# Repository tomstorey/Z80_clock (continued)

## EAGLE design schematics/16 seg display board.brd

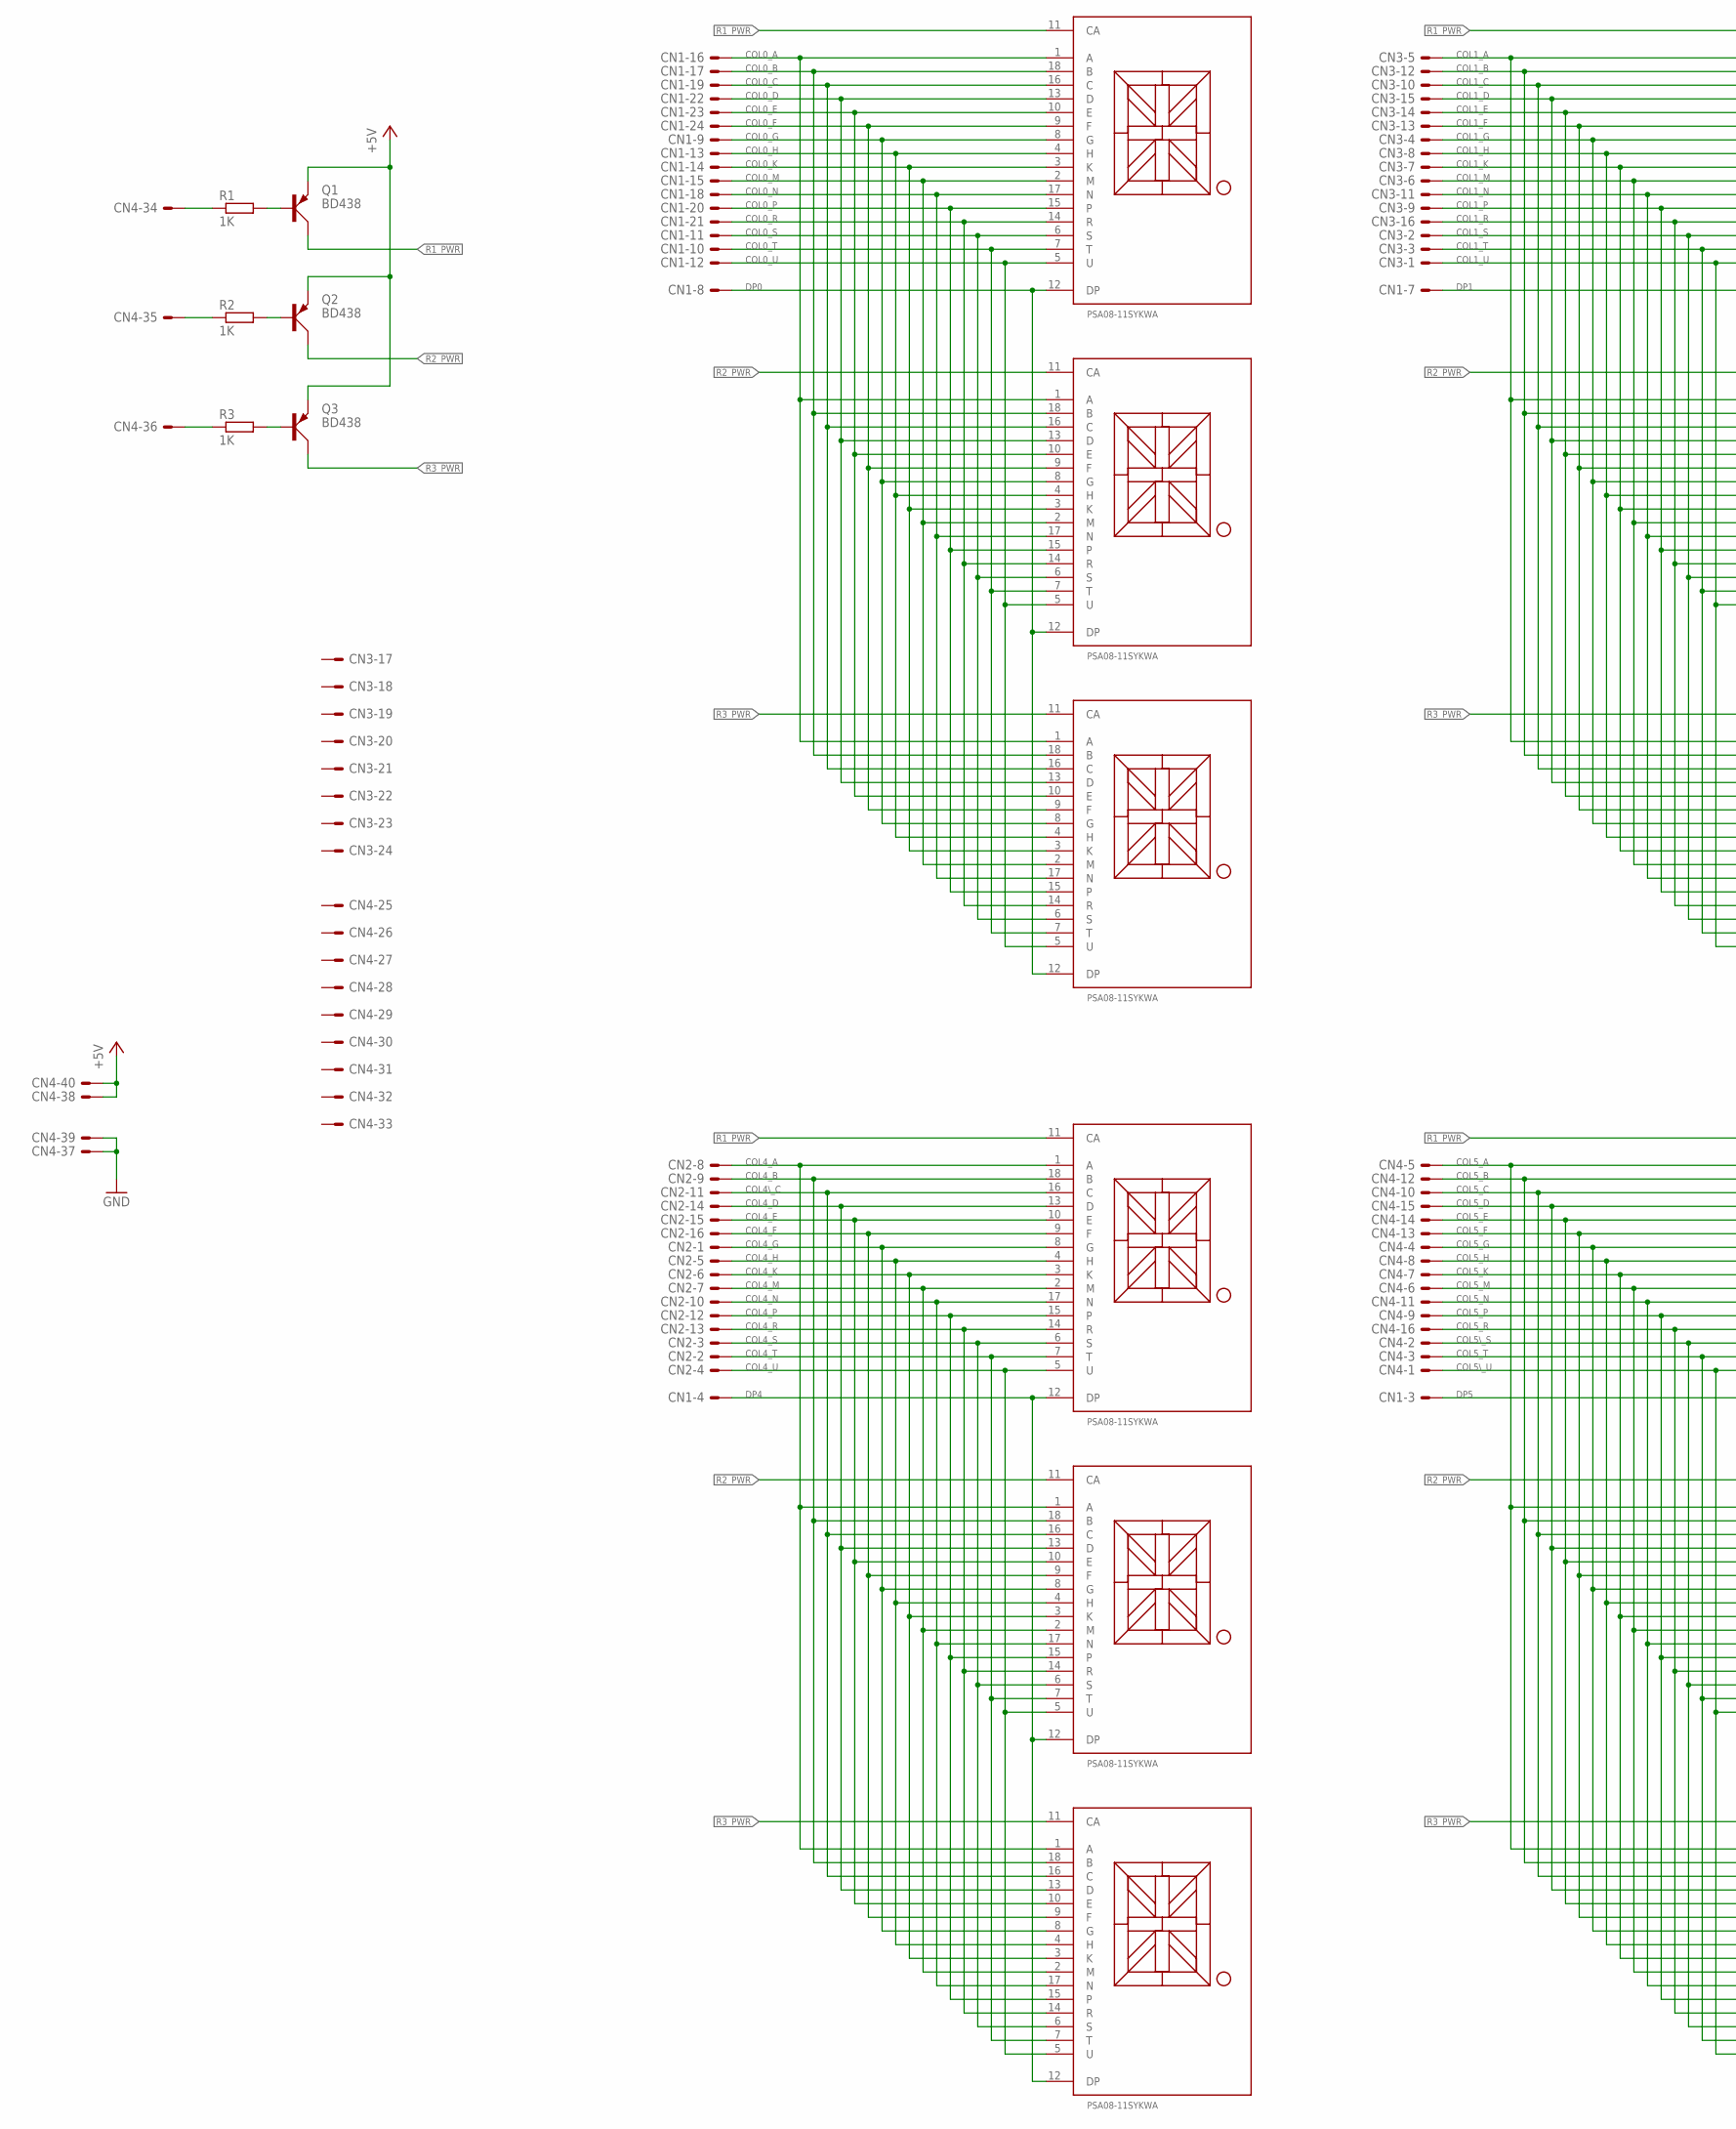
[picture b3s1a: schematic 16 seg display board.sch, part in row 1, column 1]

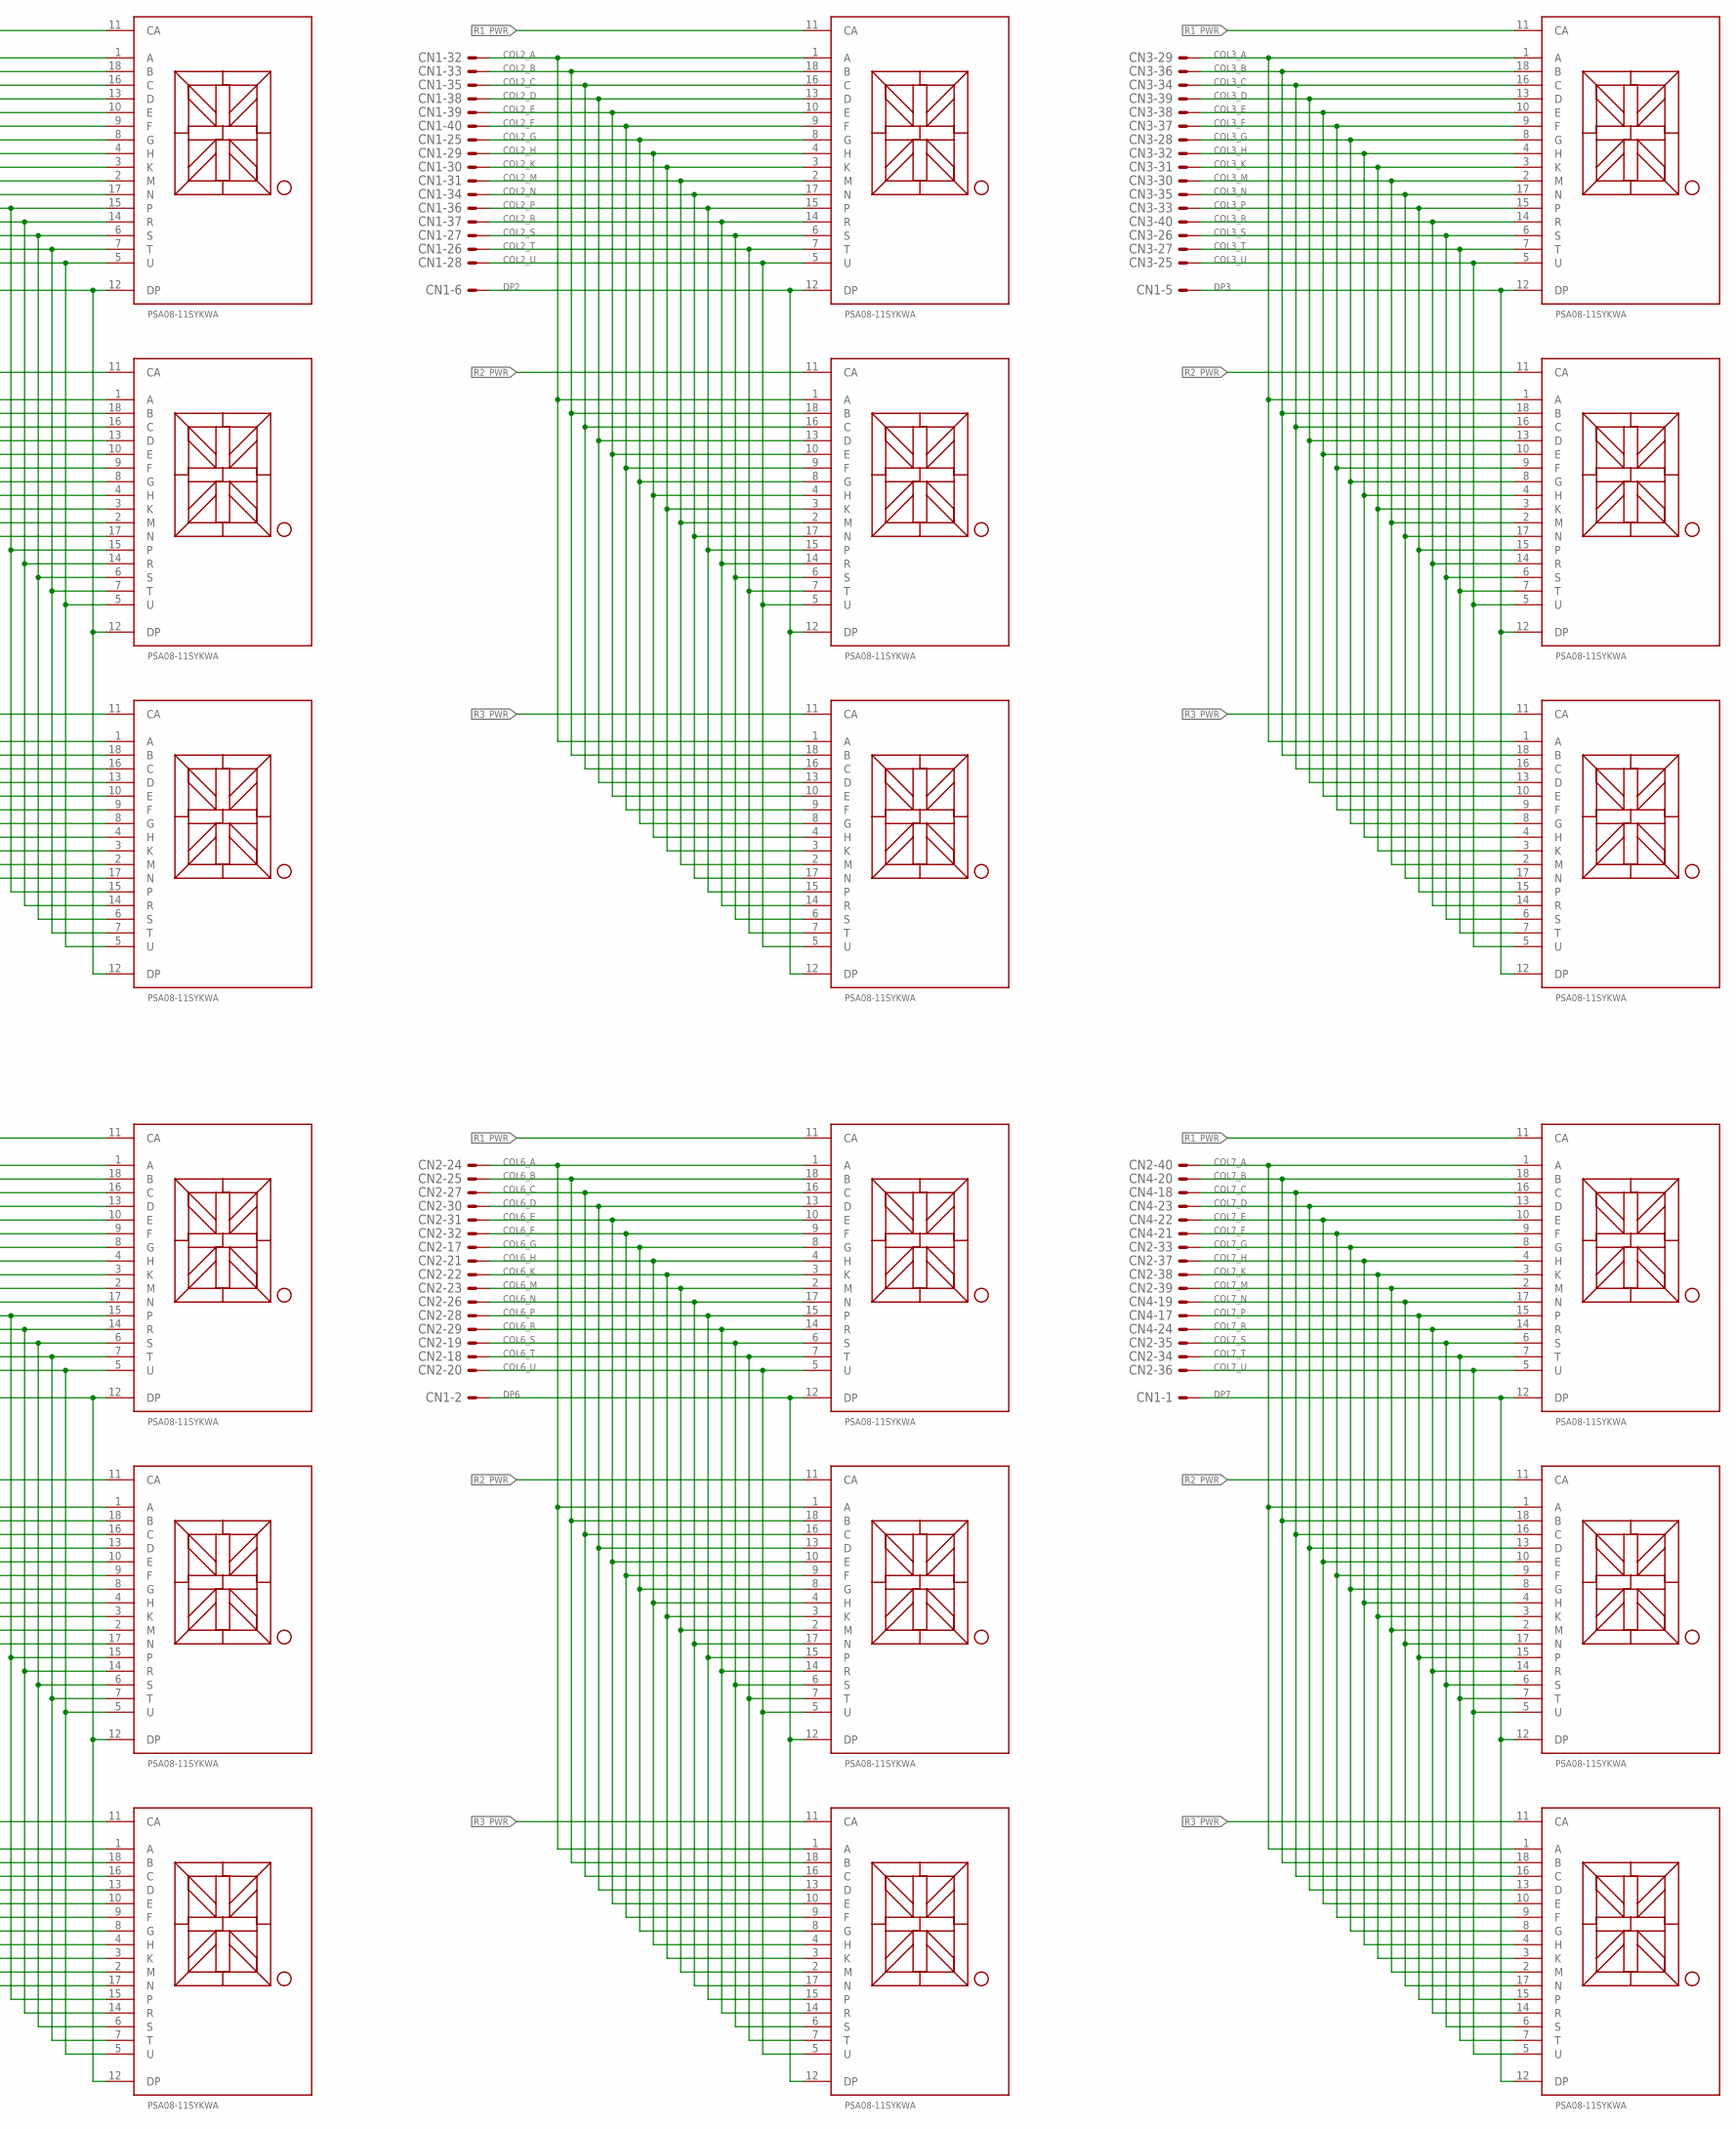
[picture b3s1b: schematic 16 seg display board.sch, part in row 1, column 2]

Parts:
CN1, CN2, CN3, CN4: HDR40
LED_R1C0, LED_R1C1, LED_R1C2, LED_R1C3, LED_R1C4, LED_R1C5, LED_R1C6, LED_R1C7, LED_R2C0, LED_R2C1, LED_R2C2, LED_R2C3, LED_R2C4, LED_R2C5, LED_R2C6, LED_R2C7, LED_R3C0, LED_R3C1, LED_R3C2, LED_R3C3, LED_R3C4, LED_R3C5, LED_R3C6, LED_R3C7: PSA08-11SYKWA
Q1, Q2, Q3: BD438; TO126AV
R1, R2, R3: 1K; 0207/10

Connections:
+5V: CN4.38, CN4.40, Q1.E, Q2.E, Q3.E
COL0_A: CN1.16, LED_R1C0.1 (A), LED_R2C0.1 (A), LED_R3C0.1 (A)
COL0_B: CN1.17, LED_R1C0.18 (B), LED_R2C0.18 (B), LED_R3C0.18 (B)
COL0_C: CN1.19, LED_R1C0.16 (C), LED_R2C0.16 (C), LED_R3C0.16 (C)
COL0_D: CN1.22, LED_R1C0.13 (D), LED_R2C0.13 (D), LED_R3C0.13 (D)
COL0_E: CN1.23, LED_R1C0.10 (E), LED_R2C0.10 (E), LED_R3C0.10 (E)
COL0_F: CN1.24, LED_R1C0.9 (F), LED_R2C0.9 (F), LED_R3C0.9 (F)
COL0_G: CN1.9, LED_R1C0.8 (G), LED_R2C0.8 (G), LED_R3C0.8 (G)
COL0_H: CN1.13, LED_R1C0.4 (H), LED_R2C0.4 (H), LED_R3C0.4 (H)
COL0_K: CN1.14, LED_R1C0.3 (K), LED_R2C0.3 (K), LED_R3C0.3 (K)
COL0_M: CN1.15, LED_R1C0.2 (M), LED_R2C0.2 (M), LED_R3C0.2 (M)
COL0_N: CN1.18, LED_R1C0.17 (N), LED_R2C0.17 (N), LED_R3C0.17 (N)
COL0_P: CN1.20, LED_R1C0.15, LED_R2C0.15, LED_R3C0.15
COL0_R: CN1.21, LED_R1C0.14 (R), LED_R2C0.14 (R), LED_R3C0.14 (R)
COL0_S: CN1.11, LED_R1C0.6 (S), LED_R2C0.6 (S), LED_R3C0.6 (S)
COL0_T: CN1.10, LED_R1C0.7 (T), LED_R2C0.7 (T), LED_R3C0.7 (T)
COL0_U: CN1.12, LED_R1C0.5 (U), LED_R2C0.5 (U), LED_R3C0.5 (U)
COL1_A: CN3.5, LED_R1C1.1 (A), LED_R2C1.1 (A), LED_R3C1.1 (A)
COL1_B: CN3.12, LED_R1C1.18 (B), LED_R2C1.18 (B), LED_R3C1.18 (B)
COL1_C: CN3.10, LED_R1C1.16 (C), LED_R2C1.16 (C), LED_R3C1.16 (C)
COL1_D: CN3.15, LED_R1C1.13 (D), LED_R2C1.13 (D), LED_R3C1.13 (D)
COL1_E: CN3.14, LED_R1C1.10 (E), LED_R2C1.10 (E), LED_R3C1.10 (E)
COL1_F: CN3.13, LED_R1C1.9 (F), LED_R2C1.9 (F), LED_R3C1.9 (F)
COL1_G: CN3.4, LED_R1C1.8 (G), LED_R2C1.8 (G), LED_R3C1.8 (G)
COL1_H: CN3.8, LED_R1C1.4 (H), LED_R2C1.4 (H), LED_R3C1.4 (H)
COL1_K: CN3.7, LED_R1C1.3 (K), LED_R2C1.3 (K), LED_R3C1.3 (K)
COL1_M: CN3.6, LED_R1C1.2 (M), LED_R2C1.2 (M), LED_R3C1.2 (M)
COL1_N: CN3.11, LED_R1C1.17 (N), LED_R2C1.17 (N), LED_R3C1.17 (N)
COL1_P: CN3.9, LED_R1C1.15, LED_R2C1.15, LED_R3C1.15
COL1_R: CN3.16, LED_R1C1.14 (R), LED_R2C1.14 (R), LED_R3C1.14 (R)
COL1_S: CN3.2, LED_R1C1.6 (S), LED_R2C1.6 (S), LED_R3C1.6 (S)
COL1_T: CN3.3, LED_R1C1.7 (T), LED_R2C1.7 (T), LED_R3C1.7 (T)
COL1_U: CN3.1, LED_R1C1.5 (U), LED_R2C1.5 (U), LED_R3C1.5 (U)
COL2_A: CN1.32, LED_R1C2.1 (A), LED_R2C2.1 (A), LED_R3C2.1 (A)
COL2_B: CN1.33, LED_R1C2.18 (B), LED_R2C2.18 (B), LED_R3C2.18 (B)
COL2_C: CN1.35, LED_R1C2.16 (C), LED_R2C2.16 (C), LED_R3C2.16 (C)
COL2_D: CN1.38, LED_R1C2.13 (D), LED_R2C2.13 (D), LED_R3C2.13 (D)
COL2_E: CN1.39, LED_R1C2.10 (E), LED_R2C2.10 (E), LED_R3C2.10 (E)
COL2_F: CN1.40, LED_R1C2.9 (F), LED_R2C2.9 (F), LED_R3C2.9 (F)
COL2_G: CN1.25, LED_R1C2.8 (G), LED_R2C2.8 (G), LED_R3C2.8 (G)
COL2_H: CN1.29, LED_R1C2.4 (H), LED_R2C2.4 (H), LED_R3C2.4 (H)
COL2_K: CN1.30, LED_R1C2.3 (K), LED_R2C2.3 (K), LED_R3C2.3 (K)
COL2_M: CN1.31, LED_R1C2.2 (M), LED_R2C2.2 (M), LED_R3C2.2 (M)
COL2_N: CN1.34, LED_R1C2.17 (N), LED_R2C2.17 (N), LED_R3C2.17 (N)
COL2_P: CN1.36, LED_R1C2.15, LED_R2C2.15, LED_R3C2.15
COL2_R: CN1.37, LED_R1C2.14 (R), LED_R2C2.14 (R), LED_R3C2.14 (R)
COL2_S: CN1.27, LED_R1C2.6 (S), LED_R2C2.6 (S), LED_R3C2.6 (S)
COL2_T: CN1.26, LED_R1C2.7 (T), LED_R2C2.7 (T), LED_R3C2.7 (T)
COL2_U: CN1.28, LED_R1C2.5 (U), LED_R2C2.5 (U), LED_R3C2.5 (U)
COL3_A: CN3.29, LED_R1C3.1 (A), LED_R2C3.1 (A), LED_R3C3.1 (A)
COL3_B: CN3.36, LED_R1C3.18 (B), LED_R2C3.18 (B), LED_R3C3.18 (B)
COL3_C: CN3.34, LED_R1C3.16 (C), LED_R2C3.16 (C), LED_R3C3.16 (C)
COL3_D: CN3.39, LED_R1C3.13 (D), LED_R2C3.13 (D), LED_R3C3.13 (D)
COL3_E: CN3.38, LED_R1C3.10 (E), LED_R2C3.10 (E), LED_R3C3.10 (E)
COL3_F: CN3.37, LED_R1C3.9 (F), LED_R2C3.9 (F), LED_R3C3.9 (F)
COL3_G: CN3.28, LED_R1C3.8 (G), LED_R2C3.8 (G), LED_R3C3.8 (G)
COL3_H: CN3.32, LED_R1C3.4 (H), LED_R2C3.4 (H), LED_R3C3.4 (H)
COL3_K: CN3.31, LED_R1C3.3 (K), LED_R2C3.3 (K), LED_R3C3.3 (K)
COL3_M: CN3.30, LED_R1C3.2 (M), LED_R2C3.2 (M), LED_R3C3.2 (M)
COL3_N: CN3.35, LED_R1C3.17 (N), LED_R2C3.17 (N), LED_R3C3.17 (N)
COL3_P: CN3.33, LED_R1C3.15, LED_R2C3.15, LED_R3C3.15
COL3_R: CN3.40, LED_R1C3.14 (R), LED_R2C3.14 (R), LED_R3C3.14 (R)
COL3_S: CN3.26, LED_R1C3.6 (S), LED_R2C3.6 (S), LED_R3C3.6 (S)
COL3_T: CN3.27, LED_R1C3.7 (T), LED_R2C3.7 (T), LED_R3C3.7 (T)
COL3_U: CN3.25, LED_R1C3.5 (U), LED_R2C3.5 (U), LED_R3C3.5 (U)
COL4\_C: CN2.11, LED_R1C4.16 (C), LED_R2C4.16 (C), LED_R3C4.16 (C)
COL4_A: CN2.8, LED_R1C4.1 (A), LED_R2C4.1 (A), LED_R3C4.1 (A)
COL4_B: CN2.9, LED_R1C4.18 (B), LED_R2C4.18 (B), LED_R3C4.18 (B)
COL4_D: CN2.14, LED_R1C4.13 (D), LED_R2C4.13 (D), LED_R3C4.13 (D)
COL4_E: CN2.15, LED_R1C4.10 (E), LED_R2C4.10 (E), LED_R3C4.10 (E)
COL4_F: CN2.16, LED_R1C4.9 (F), LED_R2C4.9 (F), LED_R3C4.9 (F)
COL4_G: CN2.1, LED_R1C4.8 (G), LED_R2C4.8 (G), LED_R3C4.8 (G)
COL4_H: CN2.5, LED_R1C4.4 (H), LED_R2C4.4 (H), LED_R3C4.4 (H)
COL4_K: CN2.6, LED_R1C4.3 (K), LED_R2C4.3 (K), LED_R3C4.3 (K)
COL4_M: CN2.7, LED_R1C4.2 (M), LED_R2C4.2 (M), LED_R3C4.2 (M)
COL4_N: CN2.10, LED_R1C4.17 (N), LED_R2C4.17 (N), LED_R3C4.17 (N)
COL4_P: CN2.12, LED_R1C4.15, LED_R2C4.15, LED_R3C4.15
COL4_R: CN2.13, LED_R1C4.14 (R), LED_R2C4.14 (R), LED_R3C4.14 (R)
COL4_S: CN2.3, LED_R1C4.6 (S), LED_R2C4.6 (S), LED_R3C4.6 (S)
COL4_T: CN2.2, LED_R1C4.7 (T), LED_R2C4.7 (T), LED_R3C4.7 (T)
COL4_U: CN2.4, LED_R1C4.5 (U), LED_R2C4.5 (U), LED_R3C4.5 (U)
COL5\_S: CN4.2, LED_R1C5.6 (S), LED_R2C5.6 (S), LED_R3C5.6 (S)
COL5\_U: CN4.1, LED_R1C5.5 (U), LED_R2C5.5 (U), LED_R3C5.5 (U)
COL5_A: CN4.5, LED_R1C5.1 (A), LED_R2C5.1 (A), LED_R3C5.1 (A)
COL5_B: CN4.12, LED_R1C5.18 (B), LED_R2C5.18 (B), LED_R3C5.18 (B)
COL5_C: CN4.10, LED_R1C5.16 (C), LED_R2C5.16 (C), LED_R3C5.16 (C)
COL5_D: CN4.15, LED_R1C5.13 (D), LED_R2C5.13 (D), LED_R3C5.13 (D)
COL5_E: CN4.14, LED_R1C5.10 (E), LED_R2C5.10 (E), LED_R3C5.10 (E)
COL5_F: CN4.13, LED_R1C5.9 (F), LED_R2C5.9 (F), LED_R3C5.9 (F)
COL5_G: CN4.4, LED_R1C5.8 (G), LED_R2C5.8 (G), LED_R3C5.8 (G)
COL5_H: CN4.8, LED_R1C5.4 (H), LED_R2C5.4 (H), LED_R3C5.4 (H)
COL5_K: CN4.7, LED_R1C5.3 (K), LED_R2C5.3 (K), LED_R3C5.3 (K)
COL5_M: CN4.6, LED_R1C5.2 (M), LED_R2C5.2 (M), LED_R3C5.2 (M)
COL5_N: CN4.11, LED_R1C5.17 (N), LED_R2C5.17 (N), LED_R3C5.17 (N)
COL5_P: CN4.9, LED_R1C5.15, LED_R2C5.15, LED_R3C5.15
COL5_R: CN4.16, LED_R1C5.14 (R), LED_R2C5.14 (R), LED_R3C5.14 (R)
COL5_T: CN4.3, LED_R1C5.7 (T), LED_R2C5.7 (T), LED_R3C5.7 (T)
COL6_A: CN2.24, LED_R1C6.1 (A), LED_R2C6.1 (A), LED_R3C6.1 (A)
COL6_B: CN2.25, LED_R1C6.18 (B), LED_R2C6.18 (B), LED_R3C6.18 (B)
COL6_C: CN2.27, LED_R1C6.16 (C), LED_R2C6.16 (C), LED_R3C6.16 (C)
COL6_D: CN2.30, LED_R1C6.13 (D), LED_R2C6.13 (D), LED_R3C6.13 (D)
COL6_E: CN2.31, LED_R1C6.10 (E), LED_R2C6.10 (E), LED_R3C6.10 (E)
COL6_F: CN2.32, LED_R1C6.9 (F), LED_R2C6.9 (F), LED_R3C6.9 (F)
COL6_G: CN2.17, LED_R1C6.8 (G), LED_R2C6.8 (G), LED_R3C6.8 (G)
COL6_H: CN2.21, LED_R1C6.4 (H), LED_R2C6.4 (H), LED_R3C6.4 (H)
COL6_K: CN2.22, LED_R1C6.3 (K), LED_R2C6.3 (K), LED_R3C6.3 (K)
COL6_M: CN2.23, LED_R1C6.2 (M), LED_R2C6.2 (M), LED_R3C6.2 (M)
COL6_N: CN2.26, LED_R1C6.17 (N), LED_R2C6.17 (N), LED_R3C6.17 (N)
COL6_P: CN2.28, LED_R1C6.15, LED_R2C6.15, LED_R3C6.15
COL6_R: CN2.29, LED_R1C6.14 (R), LED_R2C6.14 (R), LED_R3C6.14 (R)
COL6_S: CN2.19, LED_R1C6.6 (S), LED_R2C6.6 (S), LED_R3C6.6 (S)
COL6_T: CN2.18, LED_R1C6.7 (T), LED_R2C6.7 (T), LED_R3C6.7 (T)
COL6_U: CN2.20, LED_R1C6.5 (U), LED_R2C6.5 (U), LED_R3C6.5 (U)
COL7_A: CN2.40, LED_R1C7.1 (A), LED_R2C7.1 (A), LED_R3C7.1 (A)
COL7_B: CN4.20, LED_R1C7.18 (B), LED_R2C7.18 (B), LED_R3C7.18 (B)
COL7_C: CN4.18, LED_R1C7.16 (C), LED_R2C7.16 (C), LED_R3C7.16 (C)
COL7_D: CN4.23, LED_R1C7.13 (D), LED_R2C7.13 (D), LED_R3C7.13 (D)
COL7_E: CN4.22, LED_R1C7.10 (E), LED_R2C7.10 (E), LED_R3C7.10 (E)
COL7_F: CN4.21, LED_R1C7.9 (F), LED_R2C7.9 (F), LED_R3C7.9 (F)
COL7_G: CN2.33, LED_R1C7.8 (G), LED_R2C7.8 (G), LED_R3C7.8 (G)
COL7_H: CN2.37, LED_R1C7.4 (H), LED_R2C7.4 (H), LED_R3C7.4 (H)
COL7_K: CN2.38, LED_R1C7.3 (K), LED_R2C7.3 (K), LED_R3C7.3 (K)
COL7_M: CN2.39, LED_R1C7.2 (M), LED_R2C7.2 (M), LED_R3C7.2 (M)
COL7_N: CN4.19, LED_R1C7.17 (N), LED_R2C7.17 (N), LED_R3C7.17 (N)
COL7_P: CN4.17, LED_R1C7.15, LED_R2C7.15, LED_R3C7.15
COL7_R: CN4.24, LED_R1C7.14 (R), LED_R2C7.14 (R), LED_R3C7.14 (R)
COL7_S: CN2.35, LED_R1C7.6 (S), LED_R2C7.6 (S), LED_R3C7.6 (S)
COL7_T: CN2.34, LED_R1C7.7 (T), LED_R2C7.7 (T), LED_R3C7.7 (T)
COL7_U: CN2.36, LED_R1C7.5 (U), LED_R2C7.5 (U), LED_R3C7.5 (U)
DP0: CN1.8, LED_R1C0.12 (DP), LED_R2C0.12 (DP), LED_R3C0.12 (DP)
DP1: CN1.7, LED_R1C1.12 (DP), LED_R2C1.12 (DP), LED_R3C1.12 (DP)
DP2: CN1.6, LED_R1C2.12 (DP), LED_R2C2.12 (DP), LED_R3C2.12 (DP)
DP3: CN1.5, LED_R1C3.12 (DP), LED_R2C3.12 (DP), LED_R3C3.12 (DP)
DP4: CN1.4, LED_R1C4.12 (DP), LED_R2C4.12 (DP), LED_R3C4.12 (DP)
DP5: CN1.3, LED_R1C5.12 (DP), LED_R2C5.12 (DP), LED_R3C5.12 (DP)
DP6: CN1.2, LED_R1C6.12 (DP), LED_R2C6.12 (DP), LED_R3C6.12 (DP)
DP7: CN1.1, LED_R1C7.12 (DP), LED_R2C7.12 (DP), LED_R3C7.12 (DP)
GND: CN4.37, CN4.39
unnamed: Q1.B, R1.2
unnamed: Q2.B, R2.2
unnamed: Q3.B, R3.2
unnamed: CN4.34, R1.1
unnamed: CN4.35, R2.1
unnamed: CN4.36, R3.1
R1_PWR: LED_R1C0.11 (CA), LED_R1C1.11 (CA), LED_R1C2.11 (CA), LED_R1C3.11 (CA), LED_R1C4.11 (CA), LED_R1C5.11 (CA), LED_R1C6.11 (CA), LED_R1C7.11 (CA), Q1.C
R2_PWR: LED_R2C0.11 (CA), LED_R2C1.11 (CA), LED_R2C2.11 (CA), LED_R2C3.11 (CA), LED_R2C4.11 (CA), LED_R2C5.11 (CA), LED_R2C6.11 (CA), LED_R2C7.11 (CA), Q2.C
R3_PWR: LED_R3C0.11 (CA), LED_R3C1.11 (CA), LED_R3C2.11 (CA), LED_R3C3.11 (CA), LED_R3C4.11 (CA), LED_R3C5.11 (CA), LED_R3C6.11 (CA), LED_R3C7.11 (CA), Q3.C

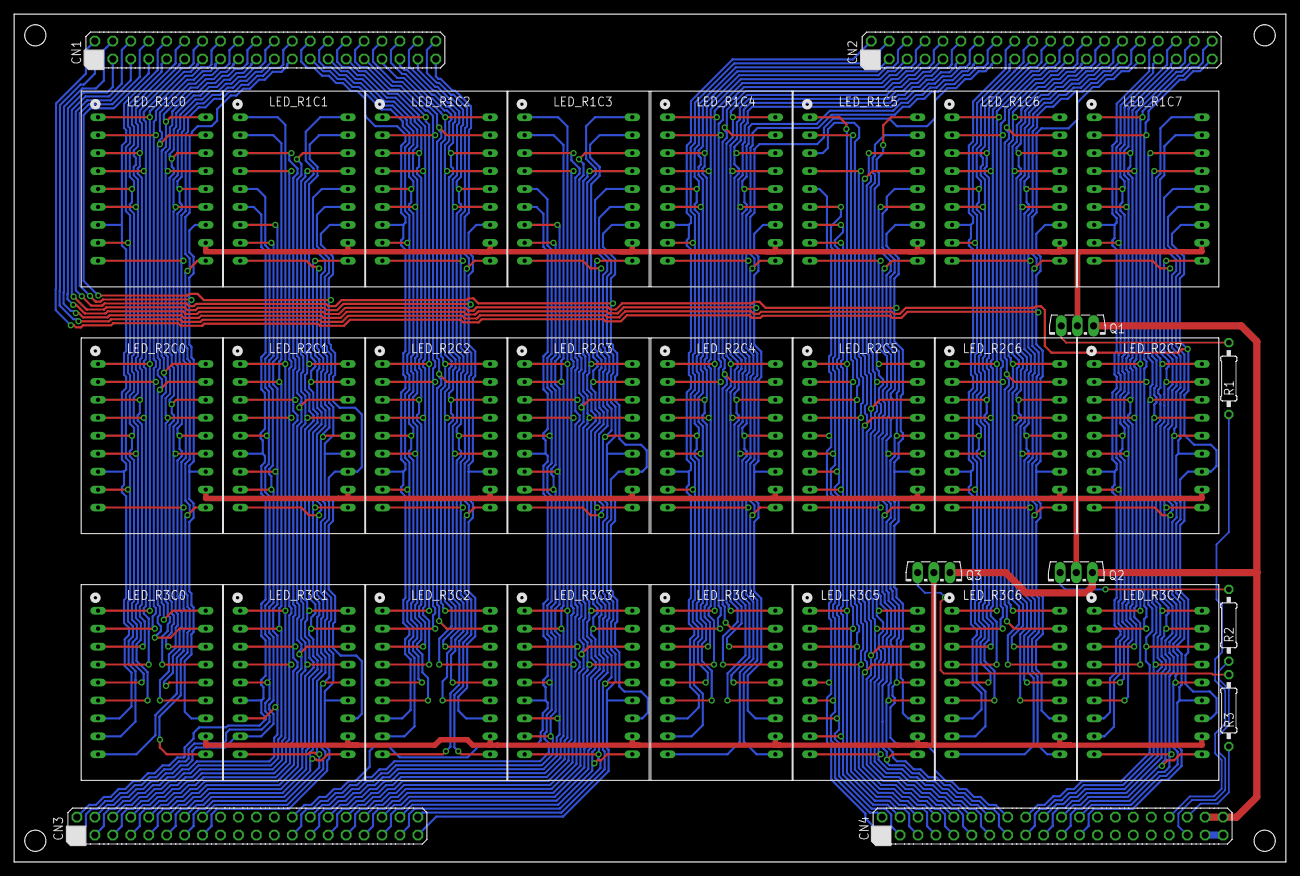
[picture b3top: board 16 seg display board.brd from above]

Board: 2 copper layers, 180.0 x 120.0 mm, 34 parts (0 on the bottom side), 147 nets.

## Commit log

2019-03-13 Add design files
2019-03-13 Update bus pins, add power and decoupling
2019-03-17 Finalise bus power pin assignments
2019-03-17 Add PSA08-11SYKWA display
2019-03-17 Reverse order of column shift regs
2019-03-17 Re-arrange order of shift registers for easier routing of wires to/from headers
2019-03-17 Re-assigned header pins to match new shift reg layout
2019-03-18 BQ4845 INT pin to CTC TRG3 for vectored RTC interrupts
2019-03-24 Fix power pins supplying display board
2019-03-28 Modify thickness of BQ4845 part outline
2019-03-31 RESET/ should not be buffered from CPU to bus
2019-03-31 Ground unused pin 13 on U3
2019-04-08 Fix DATA bus direction logic
    Off-board peripherals, e.g. CTC, need to see a certain sequence of byte reads (RETI instruction) in order to release interrupt. Original direction logic for the DATA bus did not permit this to happen.
2019-04-08 Add pull-downs to bus side of DATA buffer
2019-04-09 Slight re-arrangement
2019-04-09 Functional design
2019-04-09 Add PDFs of current design
2019-04-13 RESET/ not buffered via U3 any more
2019-04-13 Update component desigator in RC calc for POR
2019-04-28 Fix CTC interrupt vector read
    Added some more logic to allow the interrupt vector generated by the CTC to be read properly by the processor.
    The direction logic did not account for M1/ and IORQ/ going low (interrupt ack), so the data buffer was never placed in to the correct direction.
2019-04-28 Button read and beeper interrupts
2019-04-28 Size and speed optimisations for CTC Ch0 ISR
2019-04-28 Re-wrote CTC Ch0 ISR to be more compact
2019-04-30 Rename INT routines to ISRs
2019-04-30 Minor speed optimisation for CTC Ch2 ISR
2019-04-30 More small speed optimisations for CTC Ch2 ISR
2019-05-06 Start work on display refresh (CTC Ch1 ISR)
2019-05-07 Continue work on display refresh
2019-05-07 Actually, use OTIR instead of OTDR
2019-05-08 Small optimisation to CTC Ch1 ISR pre-check
2019-05-08 CTC Ch1 ISR shift DPs and write control byte
2019-05-08 CTC Ch1 ISR exit label not needed, more comments
2019-05-08 Build latest, fix typo
2019-05-09 Fix button masks
2020-03-08 A few changes:
    * renamed source files to .s
    * moved some stuff to .inc files
    * a couple of HW updates to some boars to provide a bigger RAM space for UART loading
    * SIO module for serial comms
    * serial loader code to work with the above
    * scripts for loading/reading/executing via serial
2020-03-10 Created character ROM
2020-03-10 Small changes to serial_mon
    * Restart and NMI vectors jump to RAM_BASE + offset to be useable in application
    * Before jumping to execute, wait for char to be transmitted than reset both SIO channels for use by application
2020-03-10 Change to platform.inc
    * Renamed define to serial_loading
2020-03-10 Discovered issue with Timer/RTC/IO board
    The original design of the Timer/RTC/IO board did not cater for a situation where multiple Z80 peripherals may exist in the system.
    Consequently, when M1/ and IORQ/ are both asserted by the CPU to read a vector from the interrupting peripheral, and if that peripheral happens to be the SIO, the Timer/RTC/IO board will configure it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
    Staged some logic for a subsequent modification (gates U14B and U13A) which would prevent the Timer/RTC/IO board from configuring its data bus bu
2020-03-10 Interrupt daisy chain modification
    To overcome the issue identified earlier, it seems better to change the interrupt daisy chain to make the CTC the higher priority device. This also simplifies the extra required circuitry to only a s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
    Now, only when the IEO/ signal of the CTC is asserted will the board drive the data bus to the CPU.
    Also added in a previous revision is changes to the beeper circuit. Will now be driven by a 555 timer, gated by the output register.
2020-03-10 Update .gitignore to allow .py files
2020-03-11 Changes to loader.py
    Wait for acknowledgements from the monitor that actions have completed.
2020-03-11 Changes to monitor
    * Style change, removed colons from labels
    * Emits an "Im here" signal on boot so the loader.py application knows when the monitor has started
    * Also added a ping command so that the loader script can detect the presence of the monitor
2020-03-11 Minor changes/tidy up
2020-03-11 Changes to clock code structure
    Broke a lot of things out in to separate includes to help with code manageability.
2020-03-15 Configuration app completed
    * Allows the time and date to be configured in the RTC
    * clock.s now configures CTC Ch 3 and the RTC
    * RTC generates an alarm once per minute, the CTC translates this to a vectored interrupt, and will eventually signal the clock app to update the contents of the display
2020-03-15 get_jp_table_entry macro should save DE
2020-03-15 sem_trywait and mtx_trylock macros now set the Z flag
2020-03-15 Make mutex and semaphore macros interrupt safe
2020-03-15 Add jumper to output of RST/ pin on RTC
2020-03-15 Small speed optimisation for tens of BCD
2020-03-15 Minor changes/fixes to config app
2020-03-15 Small optimisations for display refresh
2020-03-27 Implement display update effect
    Apps re-worked to update only the staging display buffers, and a small task which implements an AGC DSKY'esque update effect.
2020-03-31 Tiny performance improvement to strncpy
2020-03-31 Remove old/dead/debug code
2020-03-31 Updates:
    * Remove SIO related stuff
    * Document a few macros
    * Modify set_valid_btn_mask to OR in btn_state to btn_ack to preserve already ack'd buttons
    * Improve other elements of documentation
    * Move configr app state machine stuff out to configr_app.s
2020-03-31 Updates:
    * Moved state machine states in from clock.inc
    * Disable display update effects when entering configr, to be more responsive
    * Rename labels for each state to make them global
2020-03-31 Updates:
    * Removed debug code from reset/interrupt vectors
    * Removes SIO related stuff
    * Adjust SP to be below initialised RAM
    * Modified display effect routine to allow effects to be disabled (just does a memcpy from staging to working buffers)
2020-03-31 Huge update (basically its finished):
    * Computes time and date for selected timezones - adjusts date forward and back according to offset
    * Determines status of DST for selected timezones, adds 1 hour as required
    * Allows each row of the display to display either a time or date for any given timezone
    TODO:
    * Between certain hours, enable display dimming (use remaining bits of buttons IO register 0x08 to select which line of the display dims?)
2020-03-31 Latest build
2020-03-31 Add file
2020-03-31 Allow .rom files
2020-03-31 TZ ROM with a couple of initial/test timezones
2020-03-31 Latest build of character ROM
2020-03-31 Document TZ ROM entries a bit better
2020-03-31 Allow .md files
2020-03-31 Add readme
2020-03-31 Small fixups
2020-03-31 Introduce more button debouncing
2020-03-31 A couple of improvements
    * Fixed a bug that caused DST to end early, on month rollover
    * In cases where DST is not in effect, jump forward to display the row rather than checking if DST should be in effect
2020-03-31 Add mtx_owned macro
2020-03-31 Only increment semaphore if an app owns foreground mutex
2020-03-31 Reverse order of semaphore and mutex check
    This was done in line with changes to ctc_isr.s which only increments an apps semaphore if that app owns the foreground mutex.
    This fixes a small glitch where the semaphore was continually incremented, and if you happened to exit an app when the next apps semaphore was 0, you would return immediately to the app you just exit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
2020-03-31 Rearrange task execution order
    Rearranged such that tasks that deal with inputs run first, then applications which use that input and would provide outputs, then task that deal with outputs.
2020-03-31 Update readme with more info
2020-04-01 Add info about included Python utilities
2020-04-01 CPU schematics with corrected RAM decoding/addressing
2020-04-01 Correct schematic for new interrupt daisy chain priority
2020-04-02 Add display dimming between 2100 (on) and 0600 (off)
2020-04-02 Add BQ4845 datasheet
2020-04-02 Add photo
2020-04-02 Allow photo.jpg
2020-04-02 Build for direct ROM load
2020-04-02 Add configurable dimming, 25%/50% duty cycle
2020-04-03 Add datasheet for 16 seg displays
2020-04-04 Application structure visualisation
    Added a PDF which provides a high level overview of the application structure, including program flow from reset and interrupt vectors.
2020-04-04 Application state diagrams
    Added PDF with state diagrams for the clock and configr apps, showing how they operate.
2020-09-12 Remove original display driver board
2020-09-12 Add display driver boards as revisions
2020-09-12 Add CPLD shift register (CUPL)
2020-09-12 Annotate SW5 DIP switch positions
2020-09-12 Updates to character ROM
    * Make all character data positive logic, to suit rev B driver board
    * Add notes about differences between driver boards
2020-12-13 Dot point accomodation for sink drivers
2020-12-13 Notes/define for Rev A vs B display driver selection
2020-12-13 Small wording change
2020-12-13 Update values for U11 and U12
2020-12-13 Extend A13 to U13
2020-12-13 Some outputs from CPLD go direct
2020-12-13 Add TLC5916 LED driver
2020-12-13 Reorganise into dirs
2020-12-21 First attempt at board layout
2020-12-22 Finalise PCB layout for timer/rtc/io board
    Moved the CTC and RTC chips to the unbuffed side of the data bus, and modified direction and enable logic for data bus buffer
2020-12-22 Display PCB layout
2020-12-22 Display driver PCB layout
2020-12-22 Ignore non board, schematic or library files
2020-12-22 Unified image building
2020-12-22 New header and jumper components
2020-12-22 Space things out a little more on the board
2020-12-22 Tidy up a little
2021-11-06 A couple of small fixes and changes
    * Blank the display by writing row 0 to the control register to help avoid some aliasing that was seen
    * Post to the clock app semaphore to allow it to run immediately and populate the display staging buffers - fixes a bug where the display update seemed to skip row 0 col 0 immediately after boot
2022-06-06 Add MAME section to README
